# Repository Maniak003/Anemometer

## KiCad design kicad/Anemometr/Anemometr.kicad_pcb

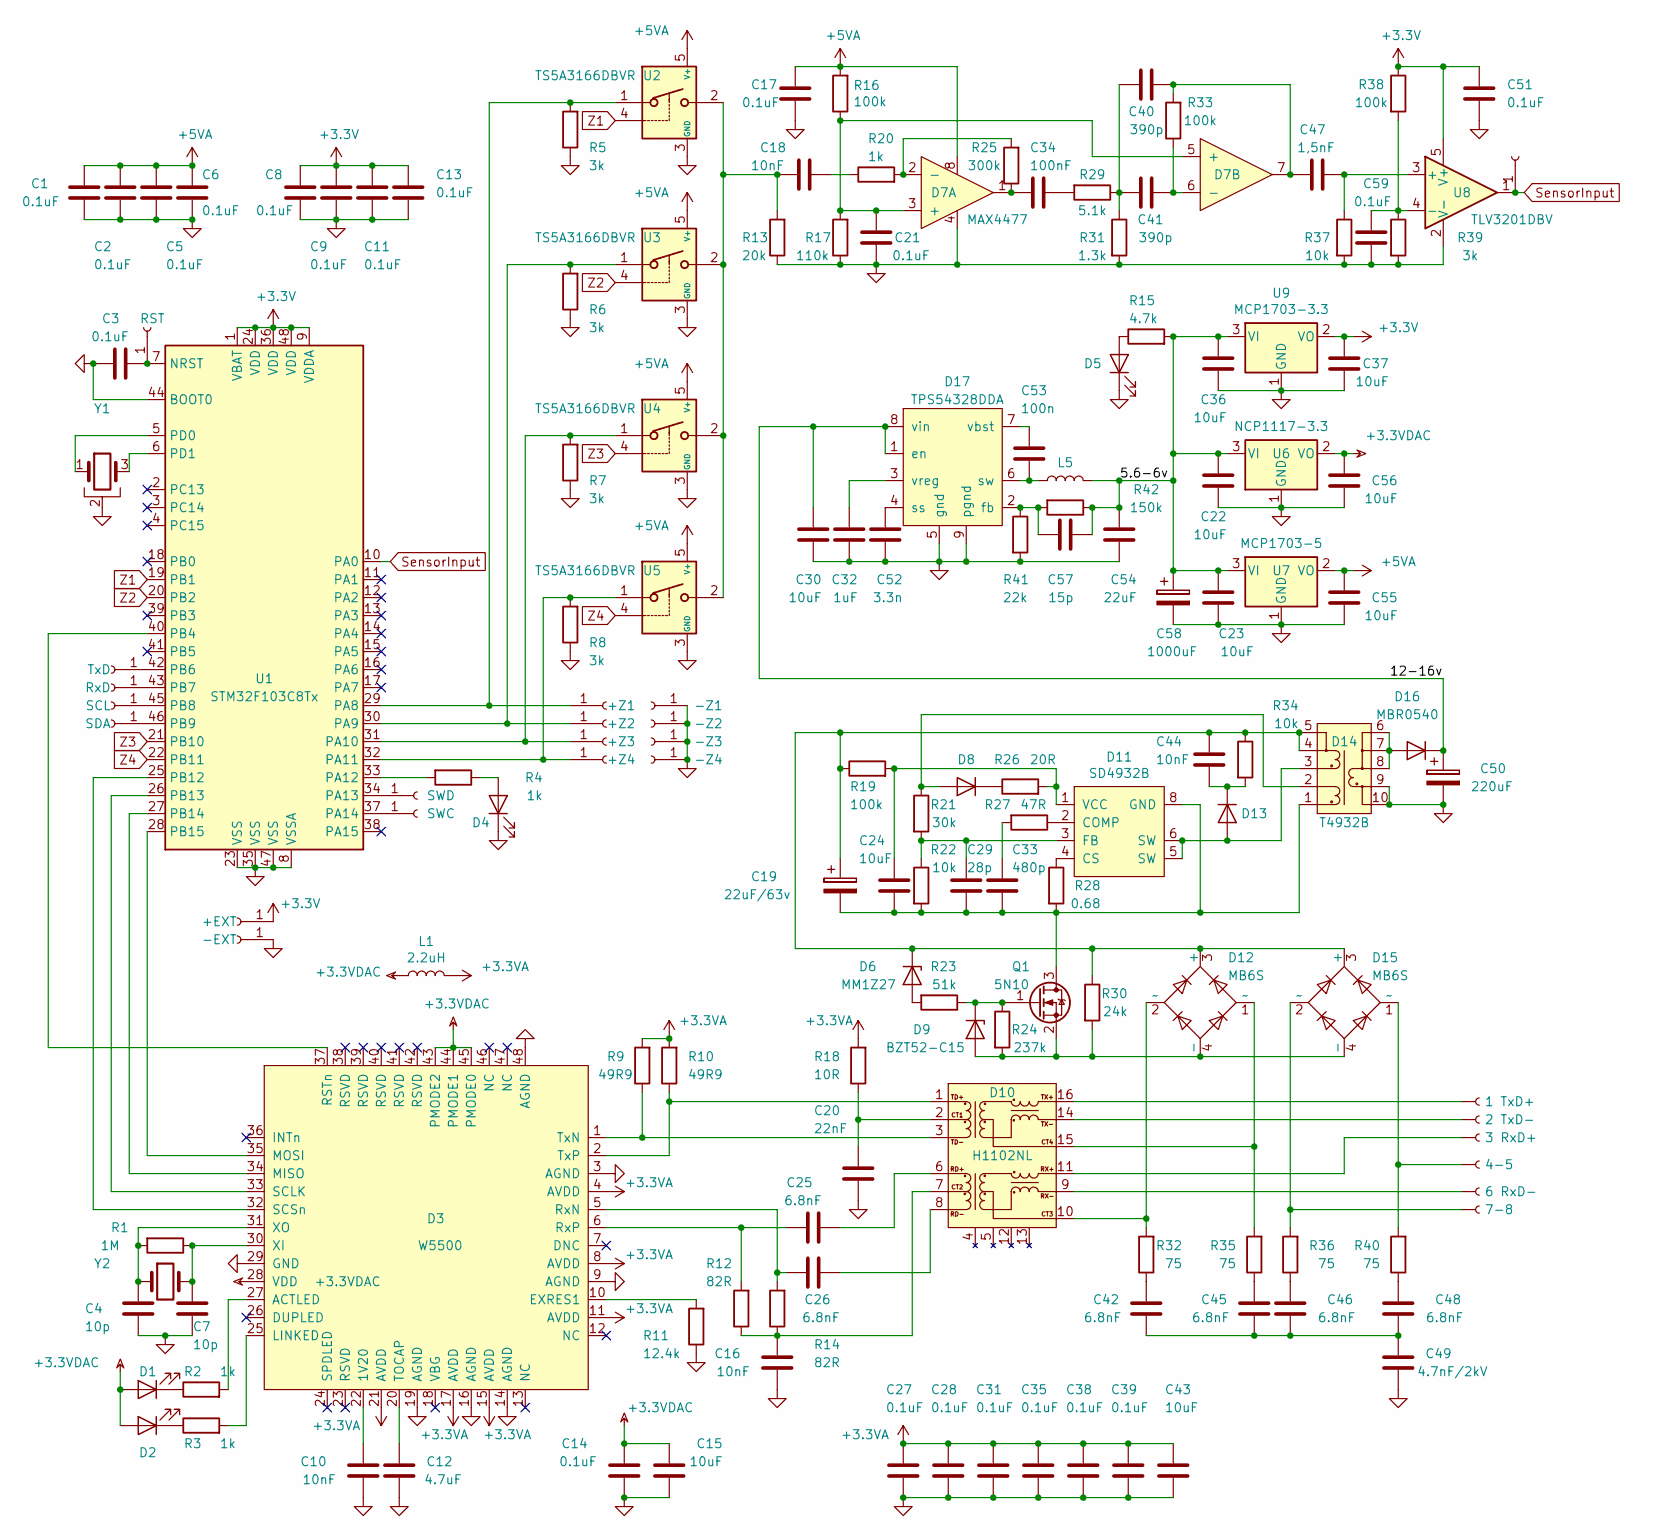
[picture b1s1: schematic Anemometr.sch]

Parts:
C1, C2, C5, C6, C8, C9, C11, C13: 0.1uF; C_0805_2012Metric
C3, C14, C17, C21, C27, C28, C31, C35, C38, C39, C51, C59: 0.1uF; C_0603_1608Metric
C4, C7: 10p; C_0603_1608Metric
C10, C16, C18, C44: 10nF; C_0603_1608Metric
C12: 4.7uF; C_0603_1608Metric
C15, C43: 10uF; C_0603_1608Metric
C19: 22uF/63v; CP_Elec_6.3x7.7
C20: 22nF; C_0603_1608Metric
C22, C23, C24, C30, C36, C37, C55, C56: 10uF; C_0805_2012Metric
C25, C26, C42, C45, C46, C48: 6.8nF; C_0603_1608Metric
C29: 28p; C_0603_1608Metric
C32: 1uF; C_0603_1608Metric
C33: 480p; C_0603_1608Metric
C34: 100nF; C_0603_1608Metric
C40, C41: 390p; C_0603_1608Metric
C47: 1,5nF; C_0603_1608Metric
C49: 4.7nF/2kV; C_1206_3216Metric
C50: 220uF; CP_EIA-7343-15_Kemet-W
C52: 3.3n; C_0603_1608Metric
C53: 100n; C_0603_1608Metric
C54: 22uF; C_1210_3225Metric
C57: 15p; C_0603_1608Metric
C58: 1000uF; CP_EIA-7343-15_Kemet-W
D1, D2, D4, D5: LED; LED_0603_1608Metric
D3: W5500; LQFP-48_7x7mm_P0.5mm
D6: MM1Z27; D_SOD-123
D7: MAX4477; MSOP-8_3x3mm_P0.65mm
D8, D13, D16: MBR0540; D_SOD-123
D9: BZT52-C15; D_SOD-123
D10: H1102NL; H1102N
D11: SD4932B; SOIC-8-N7_3.9x4.9mm_P1.27mm
D12, D15: MB6S; TO-269AA
D14: T4932B; DA2257
D17: TPS54328DDA; HSOP-8-1EP_3.9x4.9mm_P1.27mm_EP2.41x3.1mm
J1: TxD; SMD-CONN
J2: RxD; SMD-CONN
J3: SCL; SMD-CONN
J4: SDA; SMD-CONN
J5: RST; SMD-CONN
J6: +EXT; SMD-CONN
J7: -EXT; SMD-CONN
J8: SWD; SMD-CONN
J9: SWC; SMD-CONN
J10: +Z1; SMD-CONN
J11: +Z2; SMD-CONN
J12: +Z3; SMD-CONN
J13: +Z4; SMD-CONN
J14: -Z1; SMD-CONN
J15: -Z2; SMD-CONN
J16: -Z3; SMD-CONN
J17: -Z4; SMD-CONN
J18: 1 TxD+; SMD-CONN
J19: 2 TxD-; SMD-CONN
J20: 3 RxD+; SMD-CONN
J21: 4-5; SMD-CONN
J22: 6 RxD-; SMD-CONN
J23: 7-8; SMD-CONN
J24: Conn_01x01_Female; SMD-CONN
L1: 2.2uH; L_0805_2012Metric
L5: CoilCraft HLPS4018-472MR; L_Coilcraft_LPS4018
Q1: 5N10; SOT-23
R1: 1M; R_0603_1608Metric
R2, R3, R4, R20: 1k; R_0603_1608Metric
R5, R6, R7, R8, R39: 3k; R_0603_1608Metric
R9, R10: 49R9; R_0603_1608Metric
R11: 12.4k; R_0603_1608Metric
R12, R14: 82R; R_0603_1608Metric
R13: 20k; R_0603_1608Metric
R15: 4.7k; R_0603_1608Metric
R16, R19, R33, R38: 100k; R_0603_1608Metric
R17: 110k; R_0603_1608Metric
R18: 10R; R_0603_1608Metric
R21: 30k; R_0603_1608Metric
R22, R34, R37: 10k; R_0603_1608Metric
R23: 51k; R_0603_1608Metric
R24: 237k; R_0603_1608Metric
R25: 300k; R_0603_1608Metric
R26: 20R; R_0603_1608Metric
R27: 47R; R_0603_1608Metric
R28: 0.68; R_0603_1608Metric
R29: 5.1k; R_0603_1608Metric
R30: 24k; R_0603_1608Metric
R31: 1.3k; R_0603_1608Metric
R32, R35, R36, R40: 75; R_0603_1608Metric
R41: 22k; R_0603_1608Metric
R42: 150k; R_0603_1608Metric
U1: STM32F103C8Tx; LQFP-48_7x7mm_P0.5mm
U2, U3, U4, U5: TS5A3166DBVR; SOT-23-5
U6: NCP1117-3.3; SOT-223-3_TabPin2
U7: MCP1703-5; SOT-23
U8: TLV3201DBV; SOT-23-5
U9: MCP1703-3.3; SOT-23
Y1: CSTCE8M00G52A-R0; Resonator_SMD_muRata_CSTxExxV-3Pin_3.0x1.1mm
Y2: QC5CB25.0000F18B23R; Crystal_SMD_Qantek_QC5CB-2Pin_5x3.2mm

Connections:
+3.3VA: C27.1, C28.1, C31.1, C35.1, C38.1, C39.1, C43.1, D3.4 (AVDD), D3.8 (AVDD), D3.11 (AVDD), D3.15 (AVDD), D3.17 (AVDD), D3.21 (AVDD), L1.2, R9.2, R10.2, R18.2
+3.3VDAC: C14.2, C15.2, C56.2, D1.2 (A), D2.2 (A), D3.28 (VDD), D3.43 (PMODE2), D3.44 (PMODE1), D3.45 (PMODE0), L1.1, U6.2 (VO)
+3V3: C8.1, C9.1, C11.1, C13.1, C37.2, C51.1, J6.1, R38.1, U1.1 (VBAT), U1.9 (VDDA), U1.24 (VDD), U1.36 (VDD), U1.48 (VDD), U8.5 (V+), U9.2 (VO)
+5VA: C1.1, C2.1, C5.1, C6.1, C17.1, C55.2, D7.8, R16.2, U2.5 (V+), U3.5 (V+), U4.5 (V+), U5.5 (V+), U7.2 (VO)
/5.6-6v: C22.2, C23.2, C36.2, C54.2, C57.2, C58.1, L5.2, R15.2, R42.1, U6.3 (VI), U7.3 (VI), U9.3 (VI)
/12-16v: C30.2, C50.1, D16.1 (K), D17.1 (en), D17.8 (vin)
GND: C1.2, C2.2, C3.1, C4.2, C5.2, C6.2, C7.2, C8.2, C9.2, C10.1, C11.2, C12.1, C13.2, C14.1, C15.1, C16.1, C17.2, C20.2, C21.1, C22.1, C23.1, C27.2, C28.2, C30.1, C31.2, C32.1, C35.2, C36.1, C37.1, C38.2, C39.2, C43.2, C49.1, C50.2, C51.2, C52.1, C54.1, C55.1, C56.1, C58.2, C59.2, D3.3 (AGND), D3.9 (AGND), D3.14 (AGND), D3.16 (AGND), D3.19 (AGND), D3.29 (GND), D3.48 (AGND), D4.1 (K), D5.1 (K), D7.4, D14.9, D14.10, D17.5 (gnd), D17.9 (pgnd), J7.1, J14.1, J15.1, J16.1, J17.1, R5.1, R6.1, R7.1, R8.1, R11.1, R13.1, R17.1, R31.2, R37.2, R39.2, R41.2, U1.8 (VSSA), U1.23 (VSS), U1.35 (VSS), U1.44 (BOOT0), U1.47 (VSS), U2.3 (GND), U3.3 (GND), U4.3 (GND), U5.3 (GND), U6.1 (GND), U7.1 (GND), U8.2 (V-), U9.1 (GND), Y1.2
unnamed: C3.2, J5.1, U1.7 (NRST)
unnamed: C4.1, D3.31 (XO), R1.2, Y2.1
unnamed: C7.1, D3.30 (XI), R1.1, Y2.2
unnamed: C10.2, D3.22 (1V20)
unnamed: C12.2, D3.20 (TOCAP)
unnamed: C16.2, D10.7, R12.1, R14.1
unnamed: C18.1, R20.1
unnamed: C18.2, R13.2, U2.2, U3.2, U4.2, U5.2
unnamed: C19.1, C44.1, D6.1 (K), D12.3 (+), D14.4, D14.5, D15.3 (+), R19.1, R30.1, R34.1
unnamed: C19.2, C24.2, C29.2, C33.2, D11.8 (GND), D14.1, Q1.3 (D), R22.2, R28.2
unnamed: C20.1, D10.2, R18.1
unnamed: C21.2, D7.3 (+), D7.5 (+), R16.1, R17.2
unnamed: C24.1, D11.1 (VCC), R19.2, R26.2
unnamed: C25.1, D3.6 (RxP), R12.2
unnamed: C25.2, D10.6
unnamed: C26.1, D3.5 (RxN), R14.2
unnamed: C26.2, D10.8
unnamed: C29.1, D11.3 (FB), R21.2, R22.1
unnamed: C32.2, D17.3 (vreg)
unnamed: C33.1, R27.2
unnamed: C34.1, R29.2
unnamed: C34.2, D7.1, R25.1
unnamed: C40.1, C41.1, R29.1, R31.1
unnamed: C40.2, C47.1, D7.7, R33.2
unnamed: C41.2, D7.6 (-), R33.1
unnamed: C42.1, R32.1
unnamed: C42.2, C45.2, C46.2, C48.2, C49.2
unnamed: C44.2, D13.1 (K), R34.2
unnamed: C45.1, R35.1
unnamed: C46.1, R36.1
unnamed: C47.2, R37.1, U8.3 (+)
unnamed: C48.1, R40.1
unnamed: C52.2, D17.4 (ss)
unnamed: C53.1, D17.7 (vbst)
unnamed: C53.2, D17.6 (sw), L5.1
unnamed: C57.1, D17.2 (fb), R41.1, R42.2
unnamed: C59.1, R38.2, R39.1, U8.4 (-)
unnamed: D1.1 (K), R2.1
unnamed: D2.1 (K), R3.1
unnamed: D3.10 (EXRES1), R11.2
unnamed: D3.25 (LINKED), R3.2
unnamed: D3.27 (ACTLED), R2.2
unnamed: D3.32 (SCSn), U1.25 (PB12)
unnamed: D3.33 (SCLK), U1.26 (PB13)
unnamed: D3.34 (MISO), U1.27 (PB14)
unnamed: D3.35 (MOSI), U1.28 (PB15)
unnamed: D3.37 (RSTn), U1.40 (PB4)
unnamed: D4.2 (A), R4.1
unnamed: D5.2 (A), R15.1
unnamed: D6.2 (A), R23.2
unnamed: D7.2 (-), R20.2, R25.2
unnamed: D8.1 (K), R26.1
unnamed: D9.1 (K), Q1.1 (G), R23.1, R24.1
unnamed: D3.2 (TxP), D10.1, R10.1
unnamed: D3.1 (TxN), D10.3, R9.1
unnamed: D10.9, J22.1
unnamed: D10.10, D12.2 (~~), R32.2
unnamed: D10.11, J20.1
unnamed: D10.14, J19.1
unnamed: D10.15, D12.1 (~~), R35.2
unnamed: D10.16, J18.1
unnamed: D11.2 (COMP), R27.1
unnamed: D11.4 (CS), R28.1
unnamed: D11.5 (SW), D11.6 (SW), D13.2 (A), D14.3
unnamed: D9.2 (A), D12.4 (-), D15.4 (-), Q1.2 (S), R24.2, R30.2
unnamed: D8.2 (A), D14.2, R21.1
unnamed: D14.6, D14.7, D14.8, D16.2 (A)
unnamed: D15.1 (~~), J21.1, R40.2
unnamed: D15.2 (~~), J23.1, R36.2
unnamed: J1.1, U1.42 (PB6)
unnamed: J2.1, U1.43 (PB7)
unnamed: J3.1, U1.45 (PB8)
unnamed: J4.1, U1.46 (PB9)
unnamed: J8.1, U1.34 (PA13)
unnamed: J9.1, U1.37 (PA14)
unnamed: J10.1, R5.2, U1.29 (PA8), U2.1
unnamed: J11.1, R6.2, U1.30 (PA9), U3.1
unnamed: J12.1, R7.2, U1.31 (PA10), U4.1
unnamed: J13.1, R8.2, U1.32 (PA11), U5.1
unnamed: R4.2, U1.33 (PA12)
unnamed: U1.5 (PD0), Y1.1
unnamed: U1.6 (PD1), Y1.3
SensorInput: J24.1, U1.10 (PA0), U8.1
Z1: U1.19 (PB1), U2.4
Z2: U1.20 (PB2), U3.4
Z3: U1.21 (PB10), U4.4
Z4: U1.22 (PB11), U5.4

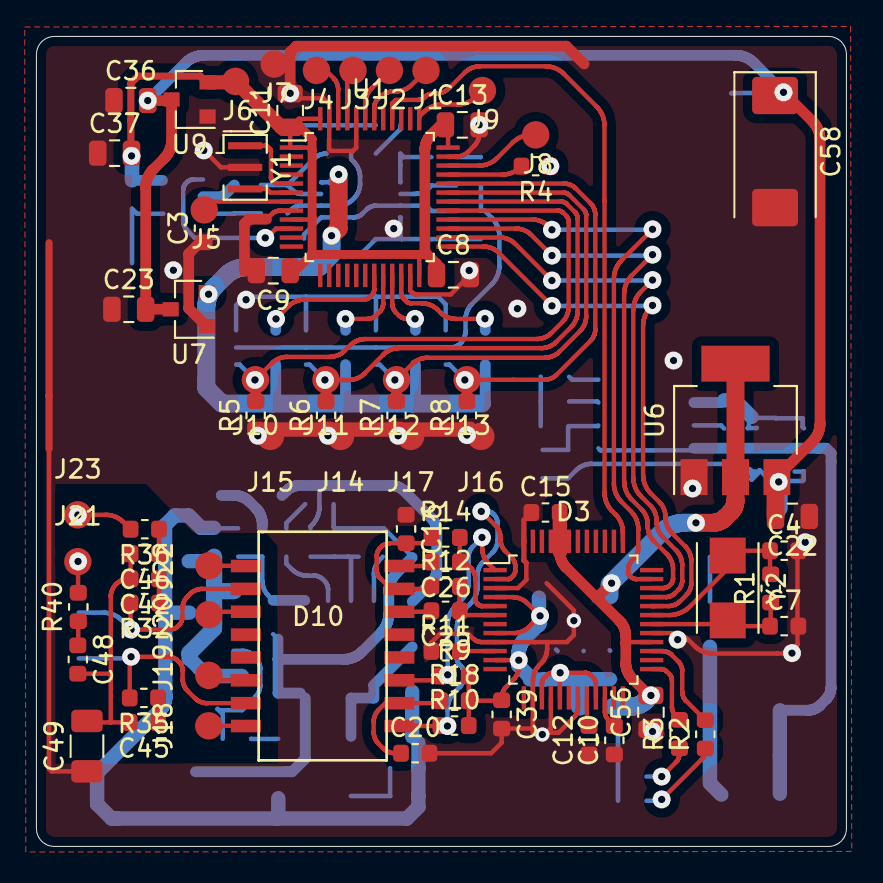
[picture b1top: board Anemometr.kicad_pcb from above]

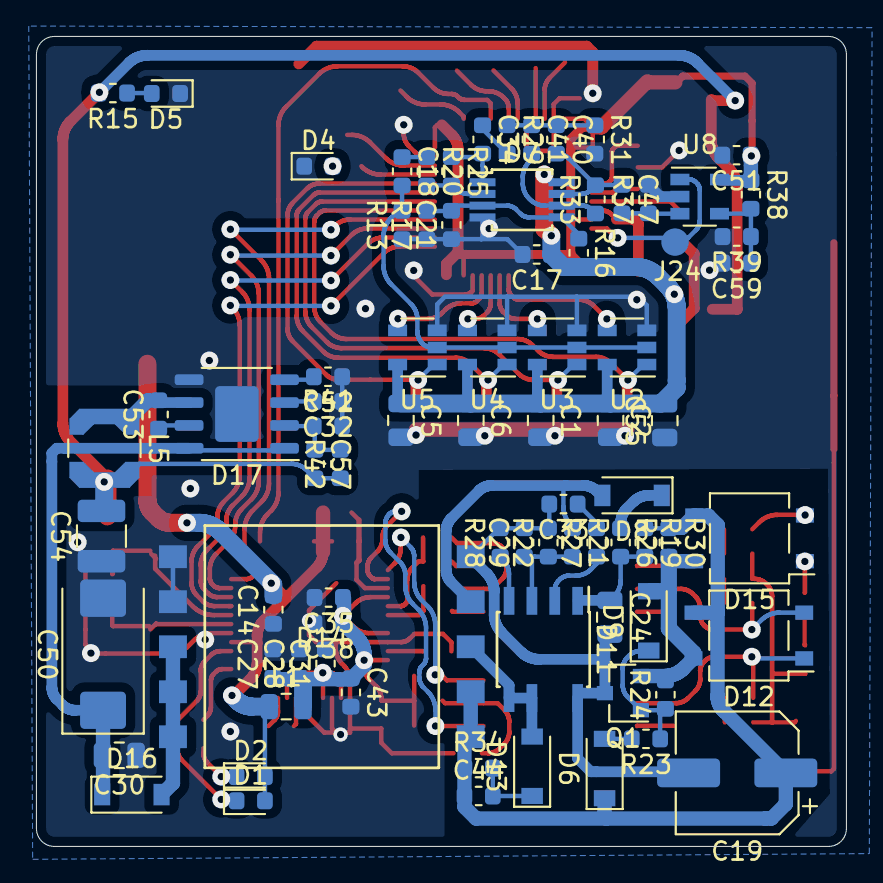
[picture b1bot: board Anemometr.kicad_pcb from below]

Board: 2 copper layers, 45.0 x 45.0 mm, 156 parts (81 on the bottom side), 94 nets.

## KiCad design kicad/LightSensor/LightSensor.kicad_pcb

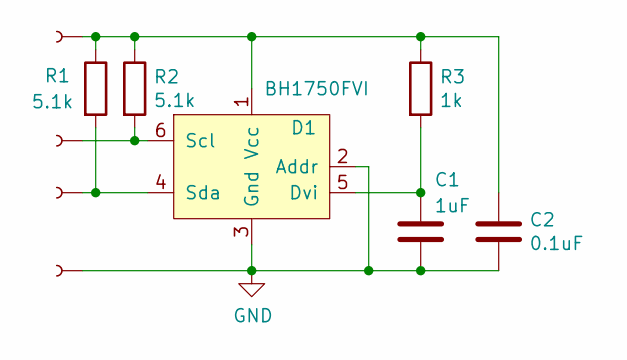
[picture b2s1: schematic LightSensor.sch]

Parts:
C1: 1uF; C_0402_1005Metric
C2: 0.1uF; C_0402_1005Metric
D1: BH1750FVI
J1, J2, J3, J4: Conn; ConnMini
R1, R2: 5.1k; R_0402_1005Metric
R3: 1k; R_0402_1005Metric

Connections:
GND: C1.2, C2.2, D1.2 (Addr), D1.3 (Gnd), J4.1
unnamed: C1.1, D1.5 (Dvi), R3.2
unnamed: C2.1, D1.1 (Vcc), J1.1, R1.1, R2.1, R3.1
unnamed: D1.4 (Sda), J3.1, R1.2
unnamed: D1.6 (Scl), J2.1, R2.2

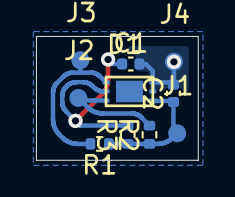
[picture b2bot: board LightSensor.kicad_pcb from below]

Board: 2 copper layers, 9.0 x 6.9 mm, 10 parts (10 on the bottom side), 5 nets.

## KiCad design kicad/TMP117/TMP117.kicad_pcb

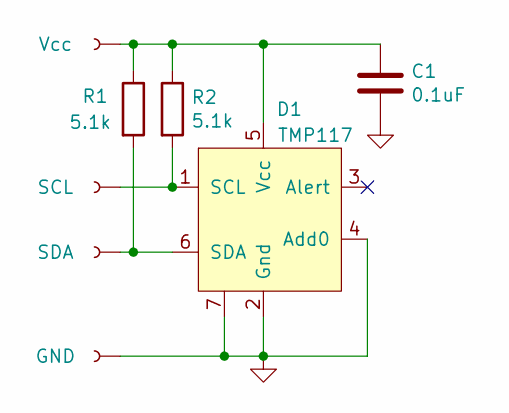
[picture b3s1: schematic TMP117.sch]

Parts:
C1: 0.1uF; C_0402_1005Metric
D1: TMP117
J1: Vcc; SMD-CONN
J2: SCL; SMD-CONN
J3: SDA; SMD-CONN
J4: GND; SMD-CONN
R1, R2: 5.1k; R_0402_1005Metric

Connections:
GND: C1.2, D1.2 (Gnd), D1.4 (Add0), D1.7, J4.1
unnamed: C1.1, D1.5 (Vcc), J1.1, R1.1, R2.1
unnamed: D1.1 (SCL), J2.1, R2.2
unnamed: D1.6 (SDA), J3.1, R1.2

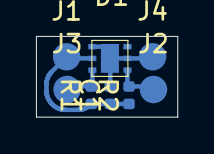
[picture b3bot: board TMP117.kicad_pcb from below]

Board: 2 copper layers, 7.8 x 4.5 mm, 8 parts (8 on the bottom side), 4 nets.
